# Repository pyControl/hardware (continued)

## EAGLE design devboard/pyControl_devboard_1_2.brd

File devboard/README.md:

# Devboard 1.2

The devboard is used to emulate pyControl behavioural hardware while developing tasks.  It has the same pyboard microcontroller as the breakout board 1.2, but instead of the 6 behaviour ports on the breakout board it has pushbuttons to emulate the DIO lines and LEDs to emulate the POW lines on each port.  It additionally has RJ45 connectors for port 3 and 4 allowing pyControl devices such as audio boards to be connected, and has the same BNC connectors as the breakout board.

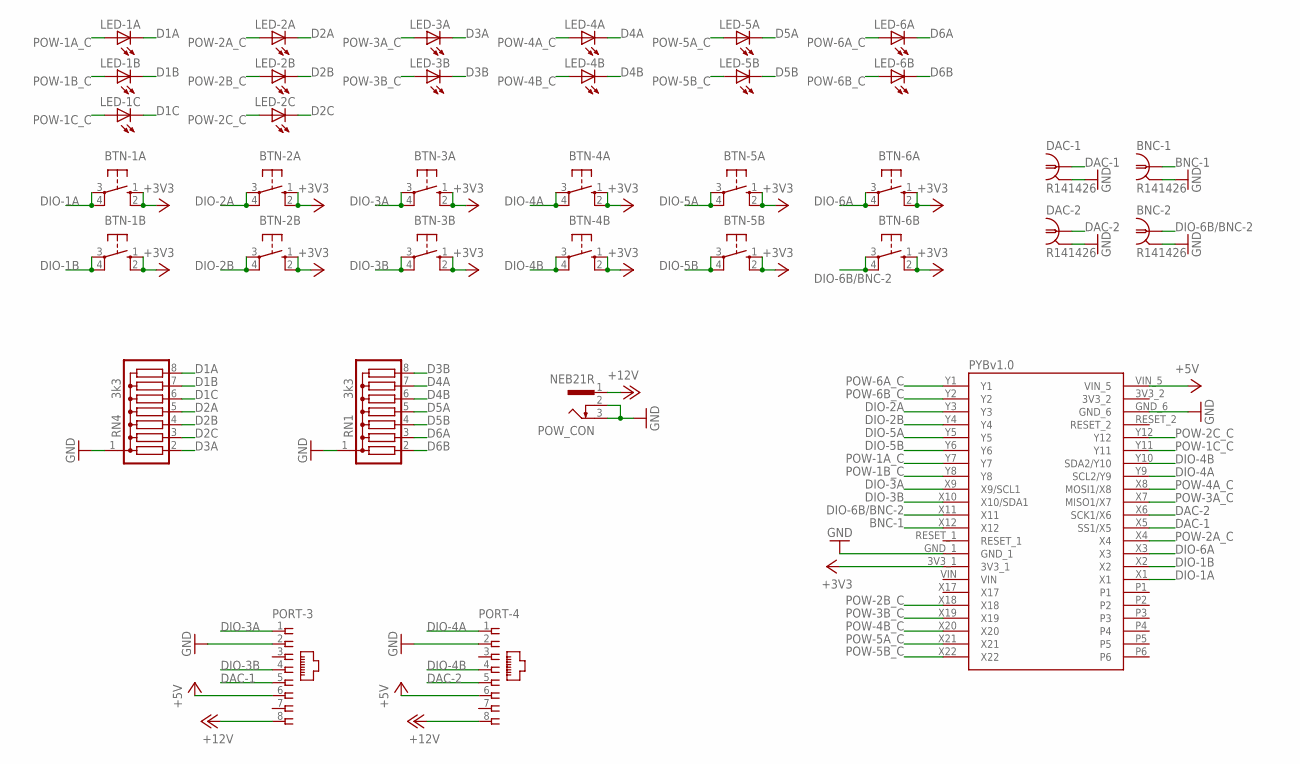
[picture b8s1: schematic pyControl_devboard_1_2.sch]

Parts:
BNC-1, BNC-2: R141426
BTN-1A, BTN-1B, BTN-2A, BTN-2B, BTN-3A, BTN-3B, BTN-4A, BTN-4B, BTN-5A, BTN-5B, BTN-6A, BTN-6B: 40-XX; B3F-40XX; MPN B3F-4000
DAC-1, DAC-2: R141426
LED-1A, LED-1B, LED-1C, LED-2A, LED-2B, LED-2C, LED-3A, LED-3B, LED-4A, LED-4B, LED-5A, LED-5B, LED-6A, LED-6B: LED3MM
PORT-3, PORT-4: RJ45VERTICAL; RJ45-NO-SHIELD-VERTICAL
POW_CON: NEB21R
PYBOARD: PYBOARD-REDUCED-2
RN1, RN4: 3k3; SIL8

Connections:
+3V3: BTN-1A.1 (S), BTN-1A.2 (S1), BTN-1B.1 (S), BTN-1B.2 (S1), BTN-2A.1 (S), BTN-2A.2 (S1), BTN-2B.1 (S), BTN-2B.2 (S1), BTN-3A.1 (S), BTN-3A.2 (S1), BTN-3B.1 (S), BTN-3B.2 (S1), BTN-4A.1 (S), BTN-4A.2 (S1), BTN-4B.1 (S), BTN-4B.2 (S1), BTN-5A.1 (S), BTN-5A.2 (S1), BTN-5B.1 (S), BTN-5B.2 (S1), BTN-6A.1 (S), BTN-6A.2 (S1), BTN-6B.1 (S), BTN-6B.2 (S1), PYBOARD.3V3_1
+5V: PORT-3.6, PORT-4.6, PYBOARD.VIN_5
+12V: PORT-3.8, PORT-4.8, POW_CON.1
BNC-1: BNC-1.1, PYBOARD.X12
D1A: LED-1A.K (C), RN4.8
D1B: LED-1B.K (C), RN4.7
D1C: LED-1C.K (C), RN4.6
D2A: LED-2A.K (C), RN4.5
D2B: LED-2B.K (C), RN4.4
D2C: LED-2C.K (C), RN4.3
D3A: LED-3A.K (C), RN4.2
D3B: LED-3B.K (C), RN1.8
D4A: LED-4A.K (C), RN1.7
D4B: LED-4B.K (C), RN1.6
D5A: LED-5A.K (C), RN1.5
D5B: LED-5B.K (C), RN1.4
D6A: LED-6A.K (C), RN1.3
D6B: LED-6B.K (C), RN1.2
DAC-1: DAC-1.1, PORT-3.5, PYBOARD.X5 (SS1/X5)
DAC-2: DAC-2.1, PORT-4.5, PYBOARD.X6 (SCK1/X6)
DIO-1A: BTN-1A.3, BTN-1A.4 (P1), PYBOARD.X1
DIO-1B: BTN-1B.3, BTN-1B.4 (P1), PYBOARD.X2
DIO-2A: BTN-2A.3, BTN-2A.4 (P1), PYBOARD.Y3
DIO-2B: BTN-2B.3, BTN-2B.4 (P1), PYBOARD.Y4
DIO-3A: BTN-3A.3, BTN-3A.4 (P1), PORT-3.1, PYBOARD.X9 (X9/SCL1)
DIO-3B: BTN-3B.3, BTN-3B.4 (P1), PORT-3.4, PYBOARD.X10 (X10/SDA1)
DIO-4A: BTN-4A.3, BTN-4A.4 (P1), PORT-4.1, PYBOARD.Y9 (SCL2/Y9)
DIO-4B: BTN-4B.3, BTN-4B.4 (P1), PORT-4.4, PYBOARD.Y10 (SDA2/Y10)
DIO-5A: BTN-5A.3, BTN-5A.4 (P1), PYBOARD.Y5
DIO-5B: BTN-5B.3, BTN-5B.4 (P1), PYBOARD.Y6
DIO-6A: BTN-6A.3, BTN-6A.4 (P1), PYBOARD.X3
DIO-6B/BNC-2: BNC-2.1, BTN-6B.3, BTN-6B.4 (P1), PYBOARD.X11
GND: BNC-1.2 (GND), BNC-1.3 (GND), BNC-1.4 (GND), BNC-1.5 (GND), BNC-2.2 (GND), BNC-2.3 (GND), BNC-2.4 (GND), BNC-2.5 (GND), DAC-1.2 (GND), DAC-1.3 (GND), DAC-1.4 (GND), DAC-1.5 (GND), DAC-2.2 (GND), DAC-2.3 (GND), DAC-2.4 (GND), DAC-2.5 (GND), PORT-3.2, PORT-4.2, POW_CON.2, POW_CON.3, PYBOARD.GND_1, PYBOARD.GND_6, RN1.1, RN4.1
POW-1A_C: LED-1A.A, PYBOARD.Y7
POW-1B_C: LED-1B.A, PYBOARD.Y8
POW-1C_C: LED-1C.A, PYBOARD.Y11
POW-2A_C: LED-2A.A, PYBOARD.X4
POW-2B_C: LED-2B.A, PYBOARD.X18
POW-2C_C: LED-2C.A, PYBOARD.Y12
POW-3A_C: LED-3A.A, PYBOARD.X7 (MISO1/X7)
POW-3B_C: LED-3B.A, PYBOARD.X19
POW-4A_C: LED-4A.A, PYBOARD.X8 (MOSI1/X8)
POW-4B_C: LED-4B.A, PYBOARD.X20
POW-5A_C: LED-5A.A, PYBOARD.X21
POW-5B_C: LED-5B.A, PYBOARD.X22
POW-6A_C: LED-6A.A, PYBOARD.Y1
POW-6B_C: LED-6B.A, PYBOARD.Y2

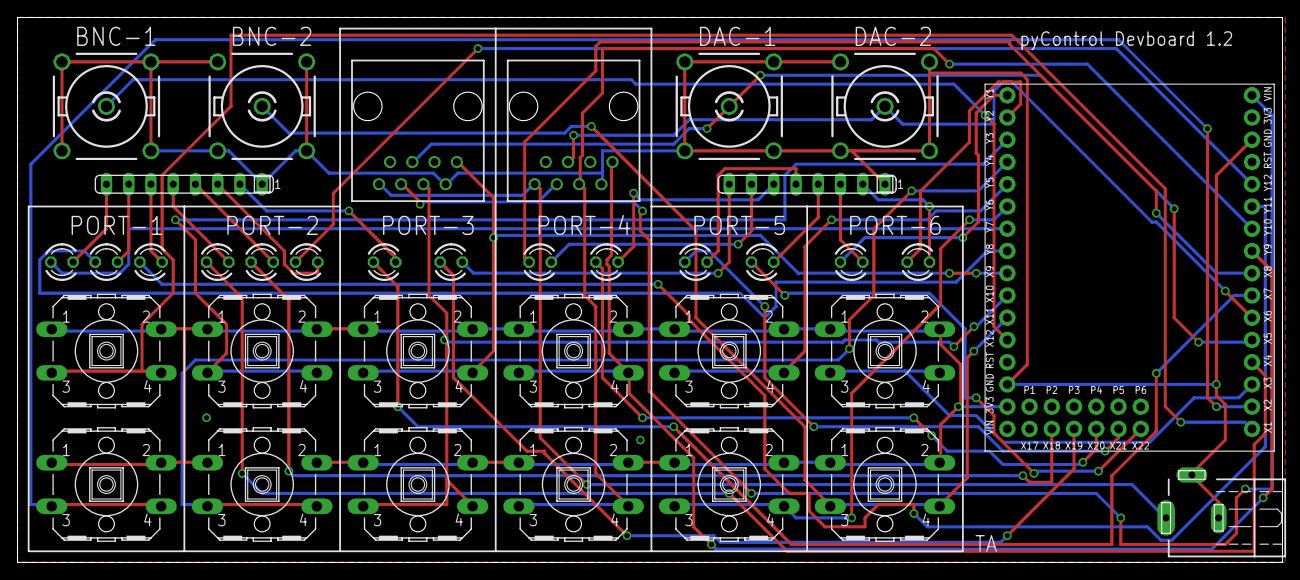
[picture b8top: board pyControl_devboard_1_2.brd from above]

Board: 2 copper layers, 144.4 x 62.2 mm, 36 parts (0 on the bottom side), 47 nets.

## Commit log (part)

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2019-07-10 Initial GIT commit.
2019-07-10 Small changes to various readme.
2019-07-15 - Fixed length of Picoblade cable on solenoid driver BOM. - Small changes to breakout board enclosure readme.
2019-07-22 Added small sound attenuating chamber design
2020-01-16 Update useful-parts-list.md
    Corrected part number of Lee products solenoid valve
2020-01-16 Readme update
    Now matches main pyControl Docs. Previously didn't mention port 1 as UART.
2020-02-13 - Behaviour_box_small: - Added holes to corners of base for mounting to floor
    - Behaviour_box_small/nine_poke_panel
    - Moved pokes 5mm upwards.
    - Changed design of poke assemly plastic parts to improve optical isolation of LEDs from different pokes.
    - Nine_poke/solenoid_driver_1_0
    - Added picoblade cable to BOM
    - Sound attenuating chamber small:
2020-12-03 - Added gerber files for all PCBs. - Added silkscreem mark indicating orientation of resistor array on breakout board.
2021-08-05 - Added breakout board mouting bracket. - Reorganised breakout board enclosure files.
2021-08-05 - Updated files for small sound attenuating chamber.
2021-08-05 - Updated the design files for the 9 port panel to use plastic parts with better isolation of stimulus LED light between ports.
2021-10-06 - Added devboard
2021-10-11 Added 3 poke panel to small behaviour box.
2021-10-22 - Added port tester board. Reorganised breakout board folder.
2023-02-02 Useful parts list: - Updated part numbers and supplier for fluid delivery components. - Added additional info about which tubing to use.
2023-07-20 - Added Solenoid_driver_RJ45 board
2024-06-13 Added load cell device
2024-08-19 Added 3x3 grid maze.
2024-11-10 Added GridMaze autocalibration system.
2025-03-28 Updated solenoid valve part number as old part was no longer manufactured
2025-07-04 Added GridMaze assembly documentation
2025-07-11 Changes to 3x3 GridMaze hardware:
    - Rather than seperate tall and short variants there is now a single intermediate height version of the maze.
    - IR illumination is now provided by IR module PCBs which connect to the maze hub board using a Molex Micro-Fit cable and can be daisy chained.
    - Reduced Poke IR beam current from 50mA to 40mA.
2025-09-15 box for 5.6mm acrylic and fusion file
2025-11-10 Added 7x7 GridMaze
2025-11-24 Updated part numbers for 7x7 maze IR module cables.
2026-06-01 Update README to include 7x7 grid maze design
2026-06-11 Updated gridmaze solenoid autocalibration
